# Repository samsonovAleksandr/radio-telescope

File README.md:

# Радиотелескоп на линии водорода · 1420,40575 МГц

Самодельный рупор 500 × 400 мм принимает излучение Млечного Пути. Усилитель SPF5189Z у зонда передаёт сигнал в RTL-SDR Blog V3, Linux-сервер записывает IQ, а браузер показывает спектр и разность ON/OFF. Для первого запуска программы достаточно встроенного демонстратора.

**Статус A2.** Электрическая схема и плата прошли ERC, DRC и сверку соединений в KiCad 10.0.8. Производственные файлы экспортированы. Docker и браузер проверены на синтетических данных. Усиление платы, согласование рупора и повторяемость небесного наблюдения предстоит измерить на собранном экземпляре. [Протокол проверок](docs/verification.md) · [Инженерный отчёт](reports/Приём%20галактического%20водорода.md)

## Комплект проекта

| Материал | Файлы |
|---|---|
| Схема и плата усилителя | [Проект KiCad с локальными библиотеками](hardware/LNA.kicad_pro) · [схема](hardware/LNA.kicad_sch) · [читаемый экспорт](hardware/schematic-kicad.svg) · [плата](hardware/LNA.kicad_pcb) · [монтаж](hardware/layout.svg) · [EAGLE SCH](hardware/LNA.sch) / [BRD](hardware/LNA.brd) |
| Изготовление | [Gerber, Excellon и карта сверления](hardware/fabrication/) · [стек, монтаж и стендовый протокол](hardware/RF.md) · [ERC](hardware/checks/erc.rpt) · [DRC и соответствие платы](hardware/checks/drc.rpt) |
| Антенна и крепление | [Размерный сборочный чертёж](antenna/assembly.svg) · [раскрой 1:1 и инструкция](antenna/README.md) · [модель седла OpenSCAD](antenna/cable-saddle.scad) · [STL](antenna/cable-saddle.stl) |
| Полный приёмник | [Соединения от зонда до USB](docs/receiver.svg) · [расчёт тракта и критерии выбора фильтра](docs/receiver.md) |
| Закупка и планирование | [Ведомость с продавцами, сметы, инструменты и сроки](docs/budget.md) · [журнал решений](docs/decisions.md) |
| Сборка и первое небо | Маршрут ниже · [стендовые испытания](hardware/RF.md) · [земля–небо, Млечный Путь, Солнце](docs/observing.md) |
| Веб-приложение | [Запуск, USB, сеть и HTTPS](docs/server.md) · [Compose](compose.yaml) · [пример конфигурации](.env.example) · [профили](web/profiles.json) · [проверки в Chrome](docs/browser-checks.md) |

## От закупки до первого наблюдения

1. **Выберите комплект.** Минимальная конфигурация оценивается в **22 478,83 ₽**, расширенная с полосовым фильтром — **28 828,83 ₽**. Сервер и принтер уже имеются. Сверьте наличие оригинального V3 и SPF5189Z, возьмите на время приборы для наладки. Сопоставьте DFM фабрики и стек с [параметрами платы](hardware/RF.md).
2. **Пока идут платы, соберите рупор и разверните приложение.** Ножницы по жести, линейка и угольник нужны для раскроя. Перед резкой измерьте контрольную линейку на шаблоне. Проверьте размеры горловины, проводимость швов, положение зонда и отражение. Если минимум S11 смещён, подберите длину зонда по [механической инструкции](antenna/README.md).
3. **Смонтируйте и испытайте усилитель.** Проверьте голую плату мультиметром, припаяйте U1 с фланцем, развязку и кабели. Первое включение выполните от лабораторного БП с ограничением 120 мА при двух нагрузках 50 Ом. Ориентир тока — 90 мА. Измерьте DC на выходе, S-параметры и отсутствие самовозбуждения. Для каждой неисправности действия приведены в [таблице приёмки](hardware/RF.md).
4. **Подключите SDR.** Проверьте полярность питания, выключенное питание bias tee, доступ к USB из контейнера и короткую пробную запись. Для 5 с при 2,4 Мвыб/с ожидаются 24 МБ CU8. Сравните уровни при двух ручных усилениях. Если форма спектра зависит от ослабления или появляются комбинационные пики, примените [проверку перегрузки](docs/receiver.md).
5. **Проверьте землю и небо, затем измерьте объект.** Начните с области Лебедя на галактическом экваторе. Запишите OFF–ON–OFF на близких высотах и с одинаковым усилением. Повторите серию со смещённым центром SDR. Проверяйте признак в абсолютных радиочастотах, отмечайте помехи, повторите наблюдение в другой день. Критерии приёмки, точность и состав журнала даны в [полевой инструкции](docs/observing.md).

Для владельца готового проекта оценка составляет **12–24 чел·ч** сборки, наладки и первого наблюдения, плюс **1–3 чел·ч** настройки сервера. Разработка и проверка комплекта с нуля — **52–88 чел·ч**. Календарный ориентир — **7–10 недель** с поставкой микросхемы либо **2–4 недели** при местном наличии U1 и SDR.

## Веб-приложение за несколько минут

Из корня проекта на Linux:

```sh
cp .env.example .env
docker compose up -d --build
```

**Адрес на сервере — http://127.0.0.1:8080/**. Для браузера на другом устройстве укажите в .env LAN-адрес сервера в LISTEN_IP и повторите `docker compose up -d`. Например, сервер с адресом 192.168.1.20 будет доступен по http://192.168.1.20:8080/. [Инструкция по запуску и передаче одного USB-устройства](docs/server.md)

Выберите «Водород Млечного Пути» → «Встроенная демонстрация». Создайте запись ON и затем OFF. Выберите первую как основную, вторую как опорную. На спектре появится широкое превышение около 1420,406 МГц. Сохраните CSV или PNG, затем нажмите «Подготовить звук» и сравните два проигрывателя. В режиме «Принятый шум» слышен перенесённый в звуковую область участок IQ. В режиме «Озвучивание измерения» высота тона следует уровню спектра.

Исходный консольный сценарий сохранён для обработки двух файлов одинаковой настройки. Команда `python spectrum.py on.iq off.iq` с установленным NumPy создаёт spectrum.csv. Параметры задаются через `--center` и `--rate` в герцах. Веб-приложение дополнительно проверяет метаданные, показывает маски и сохраняет результаты наблюдения.

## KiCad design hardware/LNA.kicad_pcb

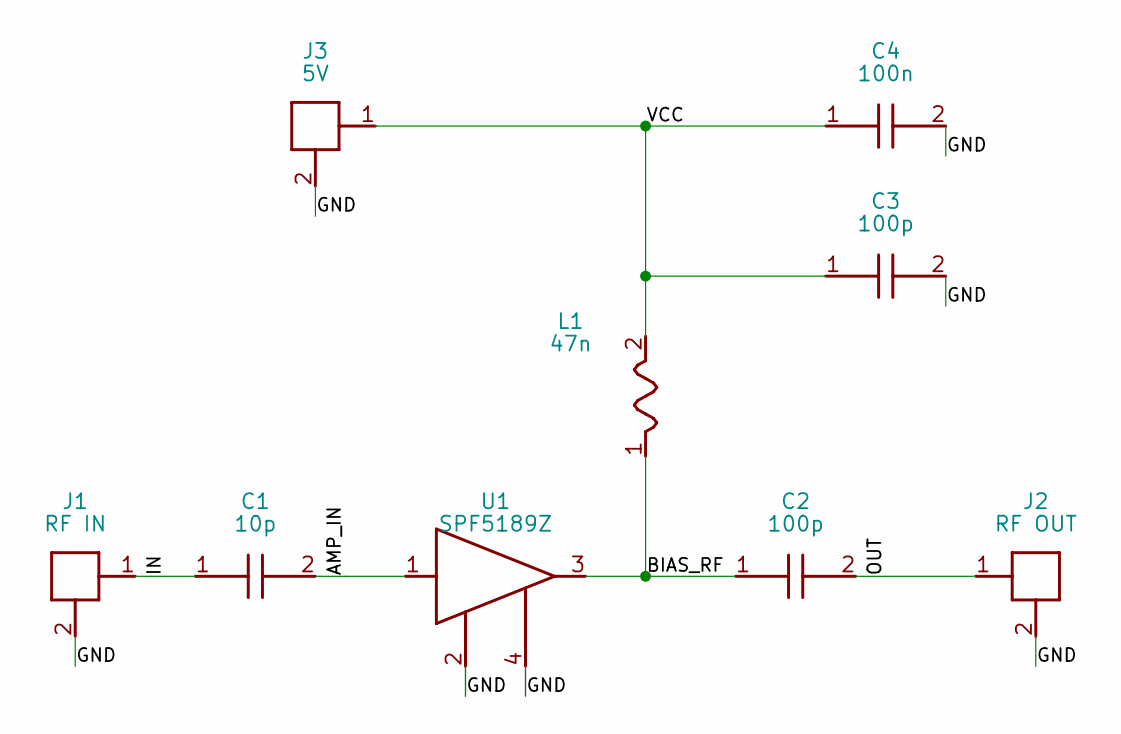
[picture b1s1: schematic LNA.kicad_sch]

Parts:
C1: 10p; CAP
C2, C3: 100p; CAP
C4: 100n; CAP
J1: RF IN; COAX
J2: RF OUT; COAX
J3: 5V; POWER
L1: 47n; CHOKE
U1: SPF5189Z; MMIC

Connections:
/AMP_IN: C1.2, U1.1 (RF_IN)
/BIAS_RF: C2.1, L1.1, U1.3 (RF_OUT/VD)
/GND: C3.2, C4.2, J1.2 (SHIELD), J2.2 (SHIELD), J3.2 (GND), U1.2 (GND), U1.4 (PADDLE)
/IN: C1.1, J1.1 (RF)
/OUT: C2.2, J2.1 (RF)
/VCC: C3.1, C4.1, J3.1 (+5V), L1.2

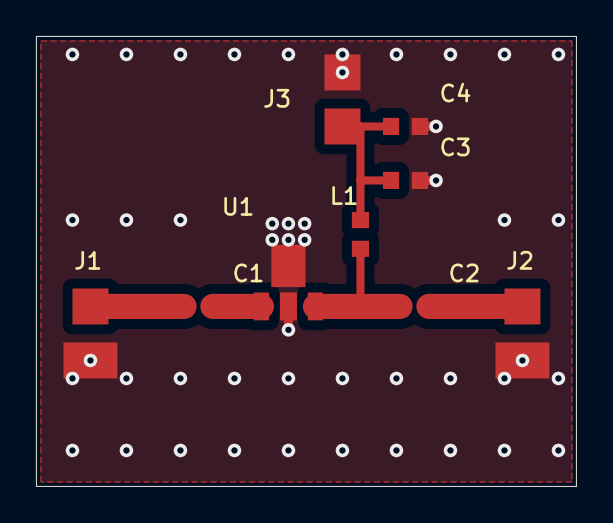
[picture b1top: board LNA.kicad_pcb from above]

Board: 2 copper layers, 30.0 x 25.0 mm, 9 parts (0 on the bottom side), 6 nets.
